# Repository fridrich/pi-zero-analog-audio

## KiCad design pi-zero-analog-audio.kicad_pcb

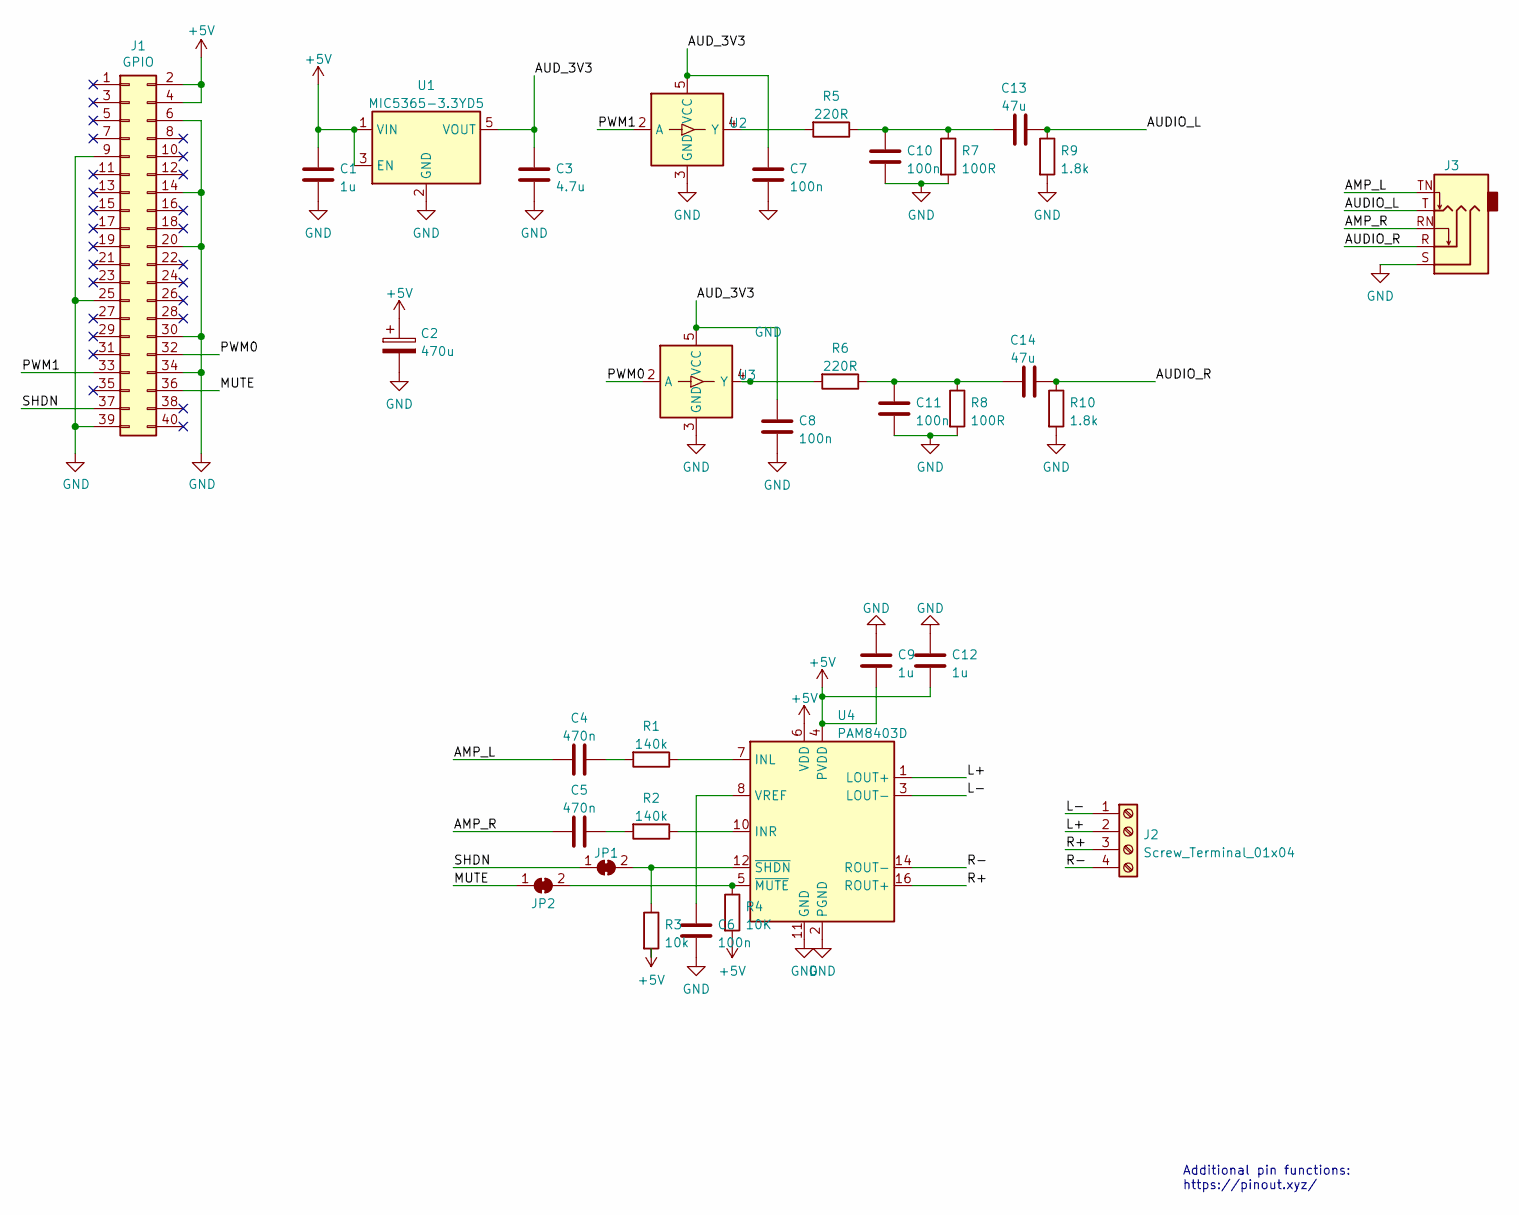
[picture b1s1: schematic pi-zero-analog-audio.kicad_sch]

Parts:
C1, C9, C12: 1u; C_0805_2012Metric_Pad1.18x1.45mm_HandSolder
C2: 470u; CP_Radial_D8.0mm_P3.50mm
C3: 4.7u; C_0805_2012Metric_Pad1.18x1.45mm_HandSolder
C4, C5: 470n; C_0805_2012Metric_Pad1.18x1.45mm_HandSolder
C6, C7, C8, C10, C11: 100n; C_0805_2012Metric_Pad1.18x1.45mm_HandSolder
C13, C14: 47u; C_0805_2012Metric_Pad1.18x1.45mm_HandSolder
J1: GPIO; PinSocket_2x20_P2.54mm_Vertical
J2: Screw_Terminal_01x04; TerminalBlock_bornier-4_P5.08mm
J3: Audio Jack; Jack_3.5mm_Ledino_KB3SPRS_Horizontal; PART_REV 1.0
JP1, JP2: SolderJumper_2_Bridged; SolderJumper-2_P1.3mm_Bridged_RoundedPad1.0x1.5mm
R1, R2: 140k; R_0805_2012Metric_Pad1.20x1.40mm_HandSolder
R3: 10k; R_0805_2012Metric_Pad1.20x1.40mm_HandSolder
R4: 10K; R_0805_2012Metric_Pad1.20x1.40mm_HandSolder
R5, R6: 220R; R_0805_2012Metric_Pad1.20x1.40mm_HandSolder
R7, R8: 100R; R_0805_2012Metric_Pad1.20x1.40mm_HandSolder
R9, R10: 1.8k; R_0805_2012Metric_Pad1.20x1.40mm_HandSolder
U1: MIC5365-3.3YD5; SOT-23-5_HandSoldering
U2, U3: MC74VHC1GT50; SOT-23-5_HandSoldering
U4: PAM8403D; SOP-16_3.9x9.9mm_P1.27mm

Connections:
+5V: C1.1, C2.1, C9.2, C12.2, J1.2, J1.4, R3.2, R4.2, U1.1 (VIN), U1.3 (EN), U4.4 (PVDD), U4.6 (VDD), U4.13 (PVDD)
/AMP_L: C4.2, J3.TN
/AMP_R: C5.2, J3.RN
/AUDIO_L: C13.2, J3.T, R9.1
/AUDIO_R: C14.2, J3.R, R10.1
/AUD_3V3: C3.1, C7.1, C8.1, U1.5 (VOUT), U2.5 (VCC), U3.5 (VCC)
/L+: J2.2, U4.1 (LOUT+)
/L-: J2.1, U4.3 (LOUT-)
/MUTE: J1.36, JP2.1 (A)
/PWM0: J1.32, U3.2 (A)
/PWM1: J1.33, U2.2 (A)
/R+: J2.3, U4.16 (ROUT+)
/R-: J2.4, U4.14 (ROUT-)
/SHDN: J1.37, JP1.1 (A)
GND: C1.2, C2.2, C3.2, C6.2, C7.2, C8.2, C9.1, C10.2, C11.2, C12.1, J1.6, J1.9, J1.14, J1.20, J1.25, J1.30, J1.34, J1.39, J3.S, R7.2, R8.2, R9.2, R10.2, U1.2 (GND), U2.3 (GND), U3.3 (GND), U4.2 (PGND), U4.11 (GND), U4.15 (PGND)
unnamed: C4.1, R1.2
unnamed: C5.1, R2.2
unnamed: C6.1, U4.8 (VREF)
unnamed: C10.1, C13.1, R5.1, R7.1
unnamed: C11.1, C14.1, R6.1, R8.1
unnamed: JP1.2 (B), R3.1, U4.12 (~SHDN)
unnamed: JP2.2 (B), R4.1, U4.5 (~MUTE)
unnamed: R1.1, U4.7 (INL)
unnamed: R2.1, U4.10 (INR)
unnamed: R5.2, U2.4 (Y)
unnamed: R6.2, U3.4 (Y)

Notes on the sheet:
Additional pin functions: https://pinout.xyz/

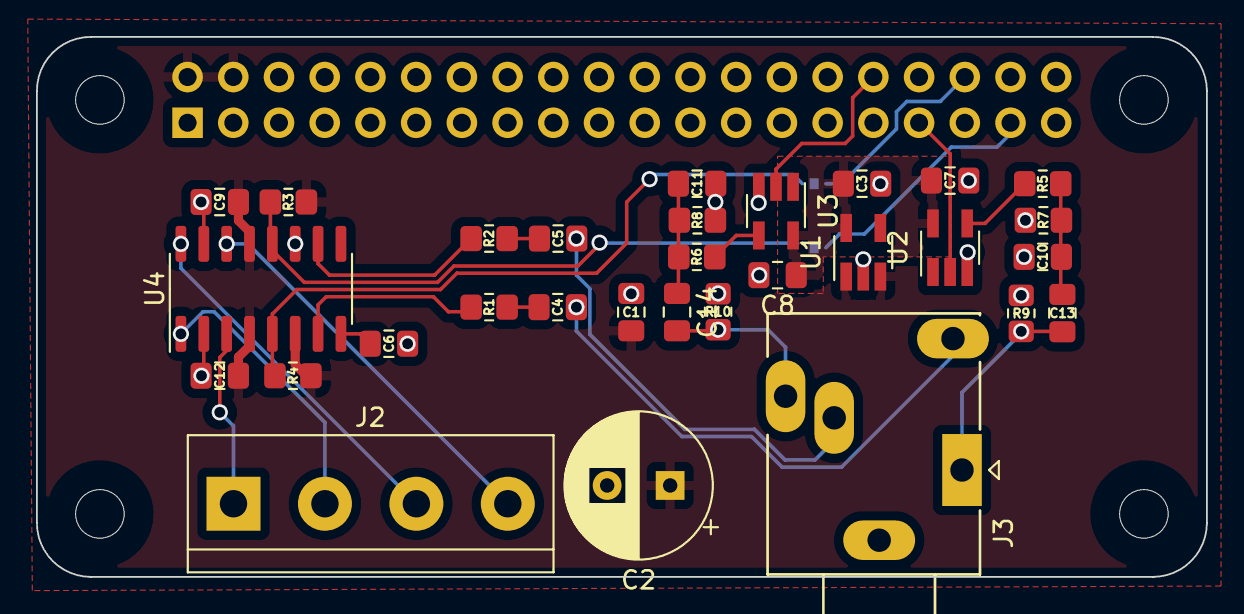
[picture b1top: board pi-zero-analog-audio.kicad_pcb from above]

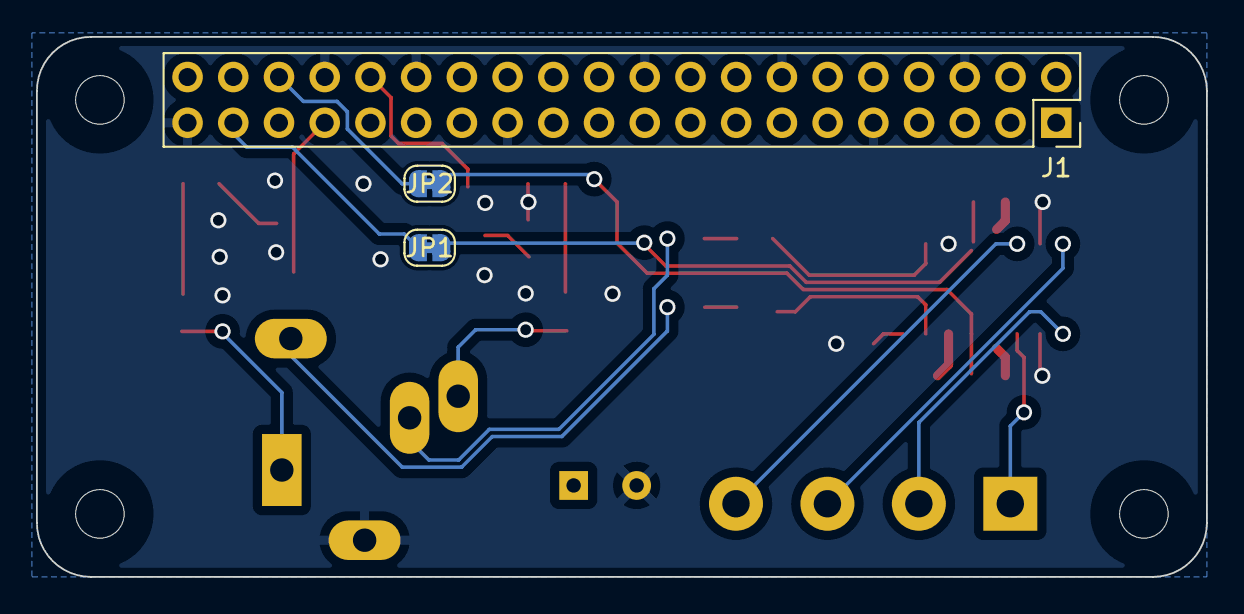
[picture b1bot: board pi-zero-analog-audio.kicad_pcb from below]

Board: 2 copper layers, 65.0 x 30.0 mm, 37 parts (3 on the bottom side), 26 nets.

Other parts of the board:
MH1, MH2, MH3, MH4: MountingHole_2.7mm_M2.5

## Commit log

2023-01-30 Starting
2023-01-30 Unrouted
2023-01-30 adding library of symbols
2023-01-30 we are using internal symbol libraries
2023-01-31 Another day starts
2023-01-31 Adding a connector for a possible Class-D amplifier
2023-01-31 Evenings come with the same regularity as the mornings
2023-01-31 Trying to adapt so that sot-23 and sc-70 elements can be used in the same footprint
2023-01-31 Vias inside the pads
2023-01-31 Adding gitignore + even more trying to make the footprint good for sc70 and sot-23
2023-02-01 Adding PAM8403D based amplifier
2023-02-01 Some more clearance of zone fixes
2023-02-01 minor cleanup
2023-02-01 Clearing the mounting holes to avoid accidental short
2023-02-02 Capacitor and resistor on the amplifier input, as per PAM8403 specs
2023-02-02 The resistor should be max 142k as per specs
2023-02-02 Some footprint changes
2023-02-03 rewrite to components that I actually can have
2023-02-03 Adding SolderJumpers for GPIO connections
2023-02-03 Changing audio connector reference and footprint
2023-02-04 Wiring the amplifier on the right side
2023-02-05 Some more efficient design with the same components
2023-02-05 Some more micro-improvements
2023-02-06 Fix error in audio jack
2023-02-06 Add more paths between +5V zones
2023-02-23 Swap two parallel capacitor and resistor in order to make soldering easier
2023-02-24 Allow alternate LDO with Band-Gap Bypass
2023-02-24 Create a footprint that can take sot-23-6 and sc-70-6 packages
2023-02-25 A little cleanup
2023-02-25 Dual gate with footprint that accepts sc-70 and sc-74
2023-02-25 Try to cater for different LDOs
2023-02-25 Some more +5V bridges
2023-02-25 cleanup the silkscreen
2023-02-25 vias to test AUD_3V3 for noise
2023-02-25 DRC run
2023-02-28 Adding a ferrite bead on 3V3 rail
2023-02-28 Adding ferrite beads on 3V3 rails
2023-02-28 shorter traces
2023-02-28 nit-picking
2023-03-08 More ground zones trying to isolate 3V3 traces
2023-03-08 Add config.txt information
2023-03-09 Two GND zones
2023-03-09 Patch to put two GND zones to avoid receiving noise
2023-03-10 Revert "Two GND zones"
    This reverts commit edaad1ef0305b16592a24cacb57811a0cb0df8b8.
2023-03-18 Do not keep current view in git
2023-03-20 Revert "Do not keep current view in git"
    This reverts commit 8480a77ddfc301b4f211528d14b5ed5f17a236e7.
2023-03-20 Revert "Do not keep current view in git"
    This reverts commit f809afe399d5978d95e506f2b499a4e50be04bc1.
2023-03-21 Ignore the views, but don't clean them
2023-04-15 some more redundance
2023-04-15 Silkscreen fixes
2024-02-28 Kicad 8
